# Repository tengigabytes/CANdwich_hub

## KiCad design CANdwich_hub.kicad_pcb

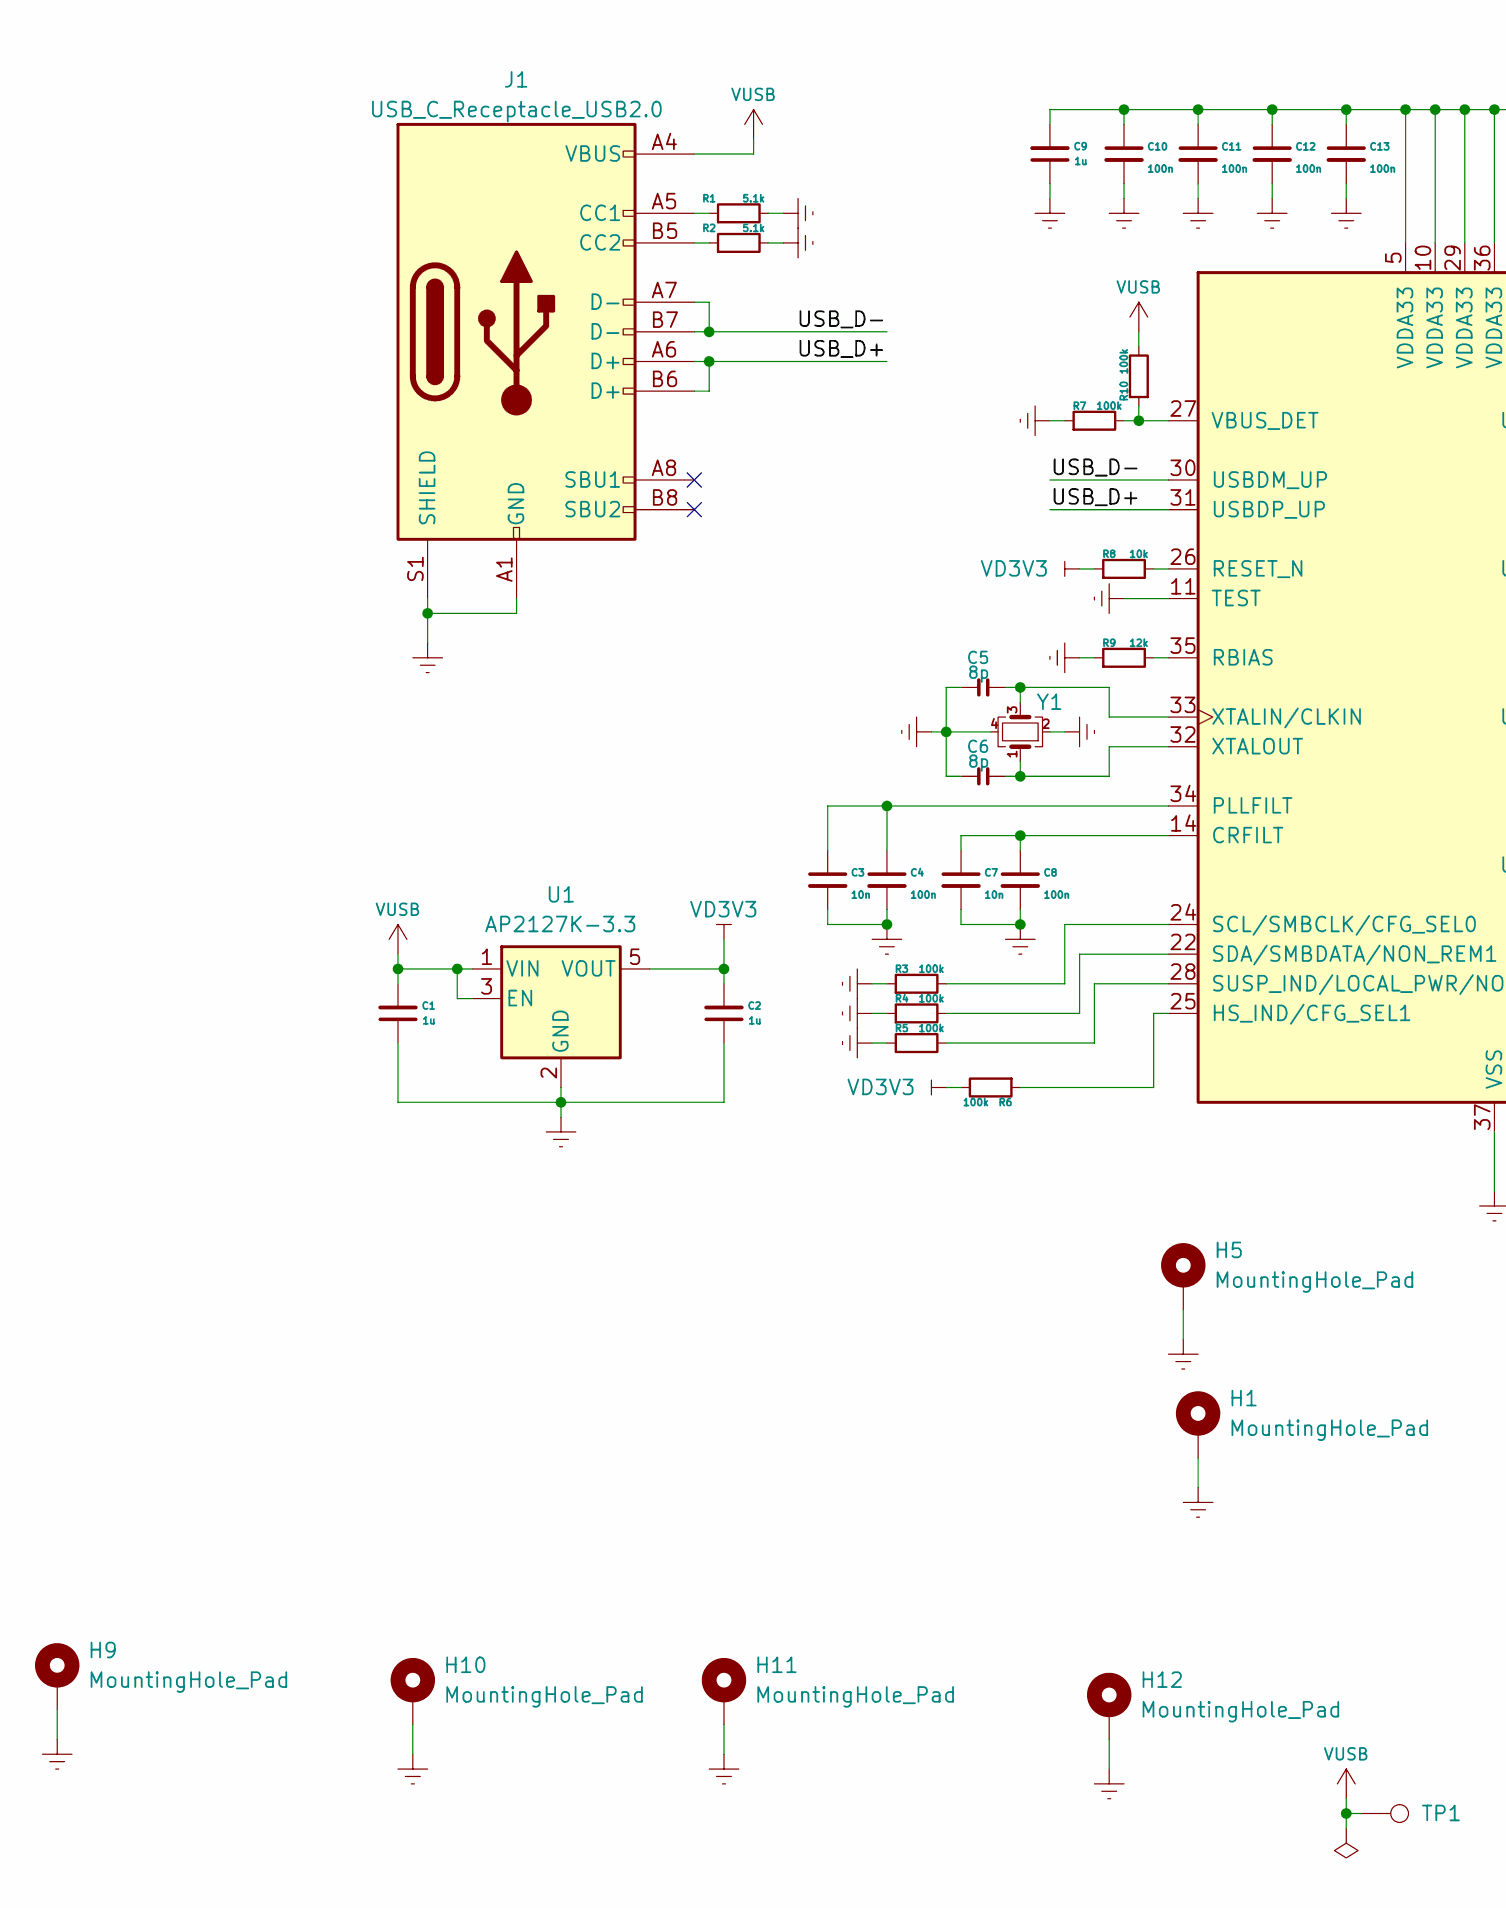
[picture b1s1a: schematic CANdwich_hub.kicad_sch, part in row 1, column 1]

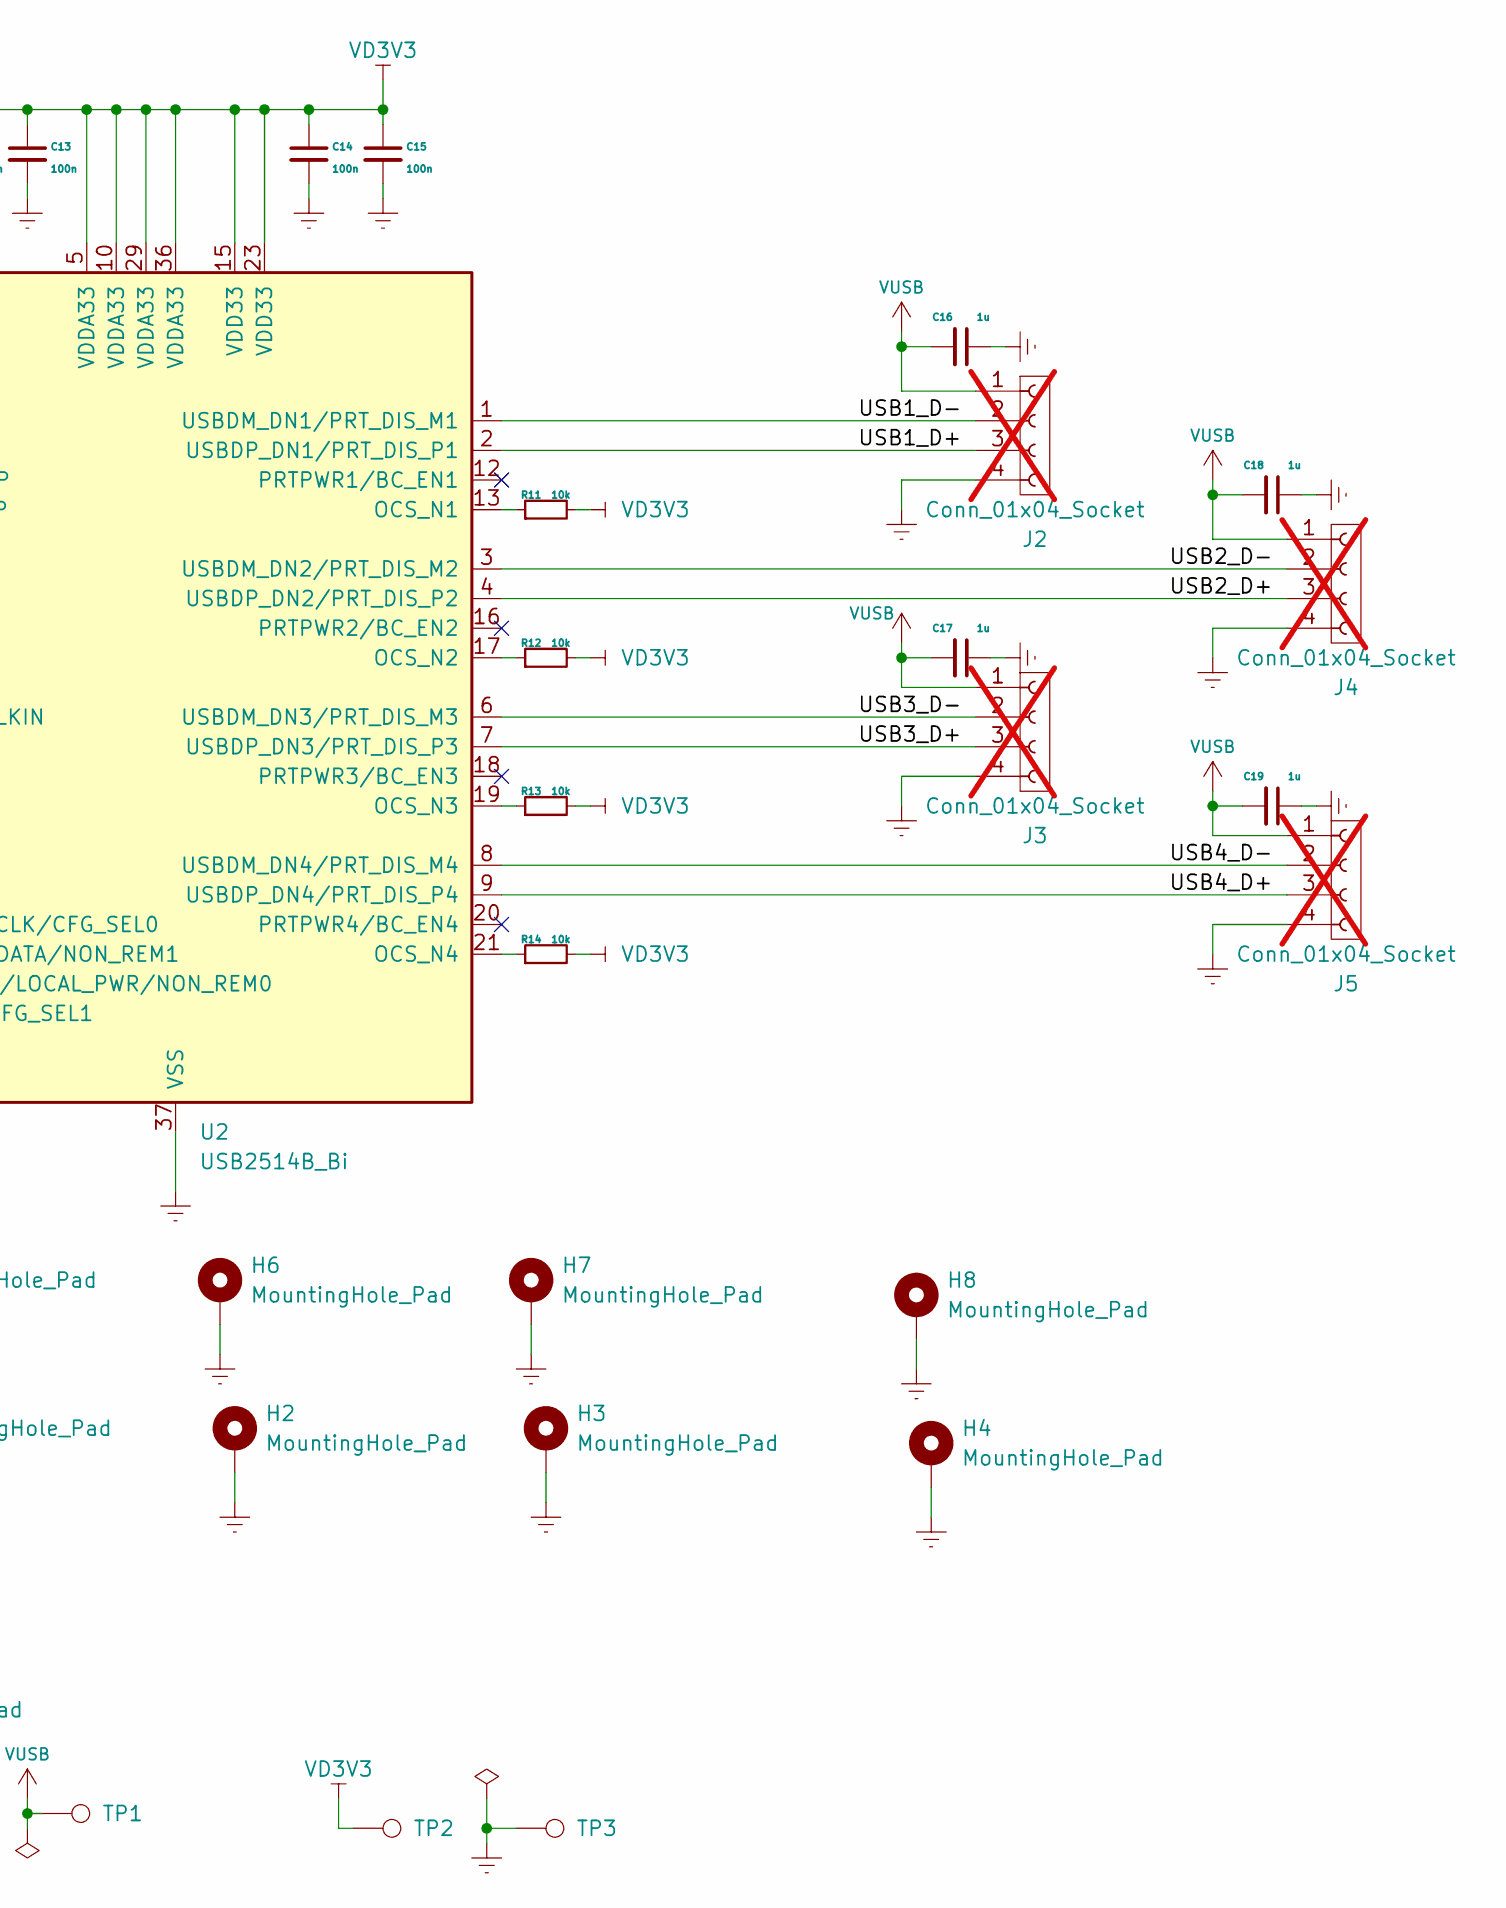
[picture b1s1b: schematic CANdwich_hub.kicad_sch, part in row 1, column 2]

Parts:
C1, C2, C9, C16, C17, C18, C19: 1u; C_0603_1608Metric; LCSC C726560
C3, C7: 10n; C_0603_1608Metric; LCSC C149618
C4, C8, C10, C11, C12, C13, C14, C15: 100n; C_0603_1608Metric; LCSC C149620
C5, C6: 8p; C_0603_1608Metric; LCSC C726543
H1, H2, H3, H4, H5, H6, H7, H8: MountingHole_Pad; USB_EdgeMount_GND_hub
H9, H10, H11, H12: MountingHole_Pad; USB_EdgeMount_GND_long
J1: USB_C_Receptacle_USB2.0; USB_C_Receptacle_XKB_U262-16XN-4BVC11; LCSC C319148
J2, J3, J4, J5: Conn_01x04_Socket; USB_EdgeMount_Hub; LCSC N/A; not fitted
R1, R2: 5.1k; R_0603_1608Metric; LCSC C105580
R3, R4, R5, R6, R7, R10: 100k; R_0603_1608Metric; LCSC C14675
R8, R11, R12, R13, R14: 10k; R_0603_1608Metric; LCSC C98220
R9: 12k; R_0603_1608Metric; LCSC C114659
TP1, TP2, TP3: TestPoint; TestPoint_Pad_D1.0mm; LCSC N/A
U1: AP2127K-3.3; SOT-23-5; LCSC C156285
U2: USB2514B_Bi; QFN-36-1EP_6x6mm_P0.5mm_EP3.7x3.7mm; LCSC C220679
Y1: 7U24000E08UCG; Crystal_SMD_3225-4Pin_3.2x2.5mm; LCSC C524739

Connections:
/USB1_D+: J2.3, U2.2 (USBDP_DN1/PRT_DIS_P1)
/USB1_D-: J2.2, U2.1 (USBDM_DN1/PRT_DIS_M1)
/USB2_D+: J4.3, U2.4 (USBDP_DN2/PRT_DIS_P2)
/USB2_D-: J4.2, U2.3 (USBDM_DN2/PRT_DIS_M2)
/USB3_D+: J3.3, U2.7 (USBDP_DN3/PRT_DIS_P3)
/USB3_D-: J3.2, U2.6 (USBDM_DN3/PRT_DIS_M3)
/USB4_D+: J5.3, U2.9 (USBDP_DN4/PRT_DIS_P4)
/USB4_D-: J5.2, U2.8 (USBDM_DN4/PRT_DIS_M4)
/USB_D+: J1.A6 (D+), J1.B6 (D+), U2.31 (USBDP_UP)
/USB_D-: J1.A7 (D-), J1.B7 (D-), U2.30 (USBDM_UP)
Earth: C1.1, C2.1, C3.2, C4.2, C5.1, C6.1, C7.2, C8.2, C9.1, C10.2, C11.2, C12.2, C13.2, C14.2, C15.2, C16.1, C17.1, C18.1, C19.1, H1.1, H2.1, H3.1, H4.1, H5.1, H6.1, H7.1, H8.1, H9.1, H10.1, H11.1, H12.1, J1.A1 (GND), J1.A12 (GND), J1.B1 (GND), J1.B12 (GND), J1.S1 (SHIELD), J2.4, J3.4, J4.4, J5.4, R1.2, R2.2, R3.1, R4.1, R5.1, R7.1, R9.1, TP3.1, U1.2 (GND), U2.11 (TEST), U2.37 (VSS), Y1.2, Y1.4
unnamed: J1.A5 (CC1), R1.1
unnamed: J1.B5 (CC2), R2.1
unnamed: C7.1, C8.1, U2.14 (CRFILT)
unnamed: R6.1, U2.25 (HS_IND/CFG_SEL1)
unnamed: R11.1, U2.13 (OCS_N1)
unnamed: R12.1, U2.17 (OCS_N2)
unnamed: R13.1, U2.19 (OCS_N3)
unnamed: R14.1, U2.21 (OCS_N4)
unnamed: C3.1, C4.1, U2.34 (PLLFILT)
unnamed: R9.2, U2.35 (RBIAS)
unnamed: R8.2, U2.26 (RESET_N)
unnamed: R3.2, U2.24 (SCL/SMBCLK/CFG_SEL0)
unnamed: R4.2, U2.22 (SDA/SMBDATA/NON_REM1)
unnamed: R5.2, U2.28 (SUSP_IND/LOCAL_PWR/NON_REM0)
unnamed: R7.2, R10.1, U2.27 (VBUS_DET)
unnamed: C5.2, U2.33 (XTALIN/CLKIN), Y1.3
unnamed: C6.2, U2.32 (XTALOUT), Y1.1
VBUS: C1.2, C16.2, C17.2, C18.2, C19.2, J1.A4 (VBUS), J1.A9 (VBUS), J1.B4 (VBUS), J1.B9 (VBUS), J2.1, J3.1, J4.1, J5.1, R10.2, TP1.1, U1.1 (VIN), U1.3 (EN)
VD3V3: C2.2, C9.2, C10.1, C11.1, C12.1, C13.1, C14.1, C15.1, R6.2, R8.1, R11.2, R12.2, R13.2, R14.2, TP2.1, U1.5 (VOUT), U2.5 (VDDA33), U2.10 (VDDA33), U2.15 (VDD33), U2.23 (VDD33), U2.29 (VDDA33), U2.36 (VDDA33)

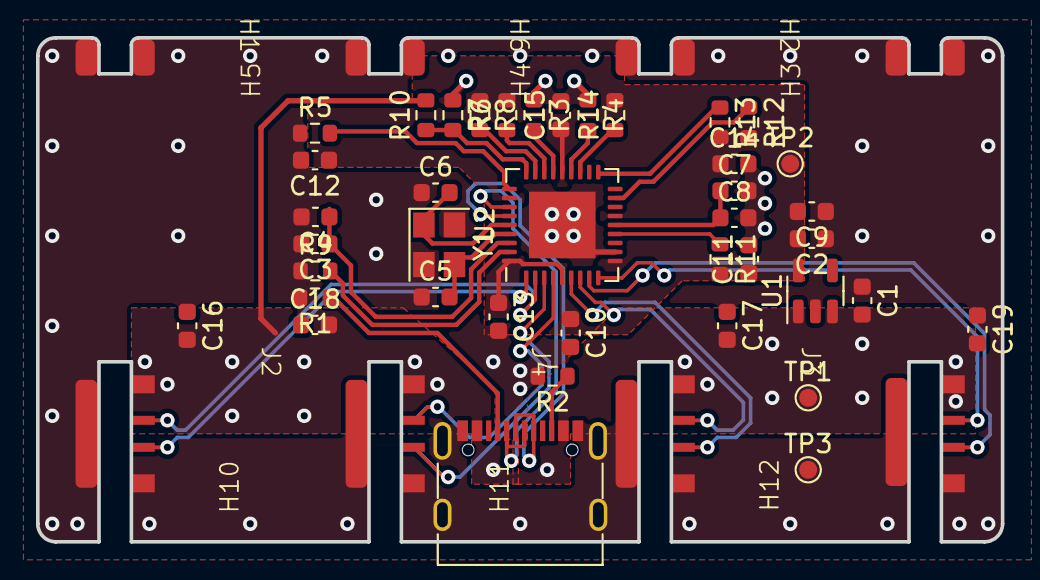
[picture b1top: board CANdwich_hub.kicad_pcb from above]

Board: 4 copper layers, 53.6 x 28.0 mm, 56 parts (0 on the bottom side), 30 nets.

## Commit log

2023-06-19 CANDwich_hub create repository
2023-06-26 Footprint placement
2023-06-29 Change stack up to 4 layers
